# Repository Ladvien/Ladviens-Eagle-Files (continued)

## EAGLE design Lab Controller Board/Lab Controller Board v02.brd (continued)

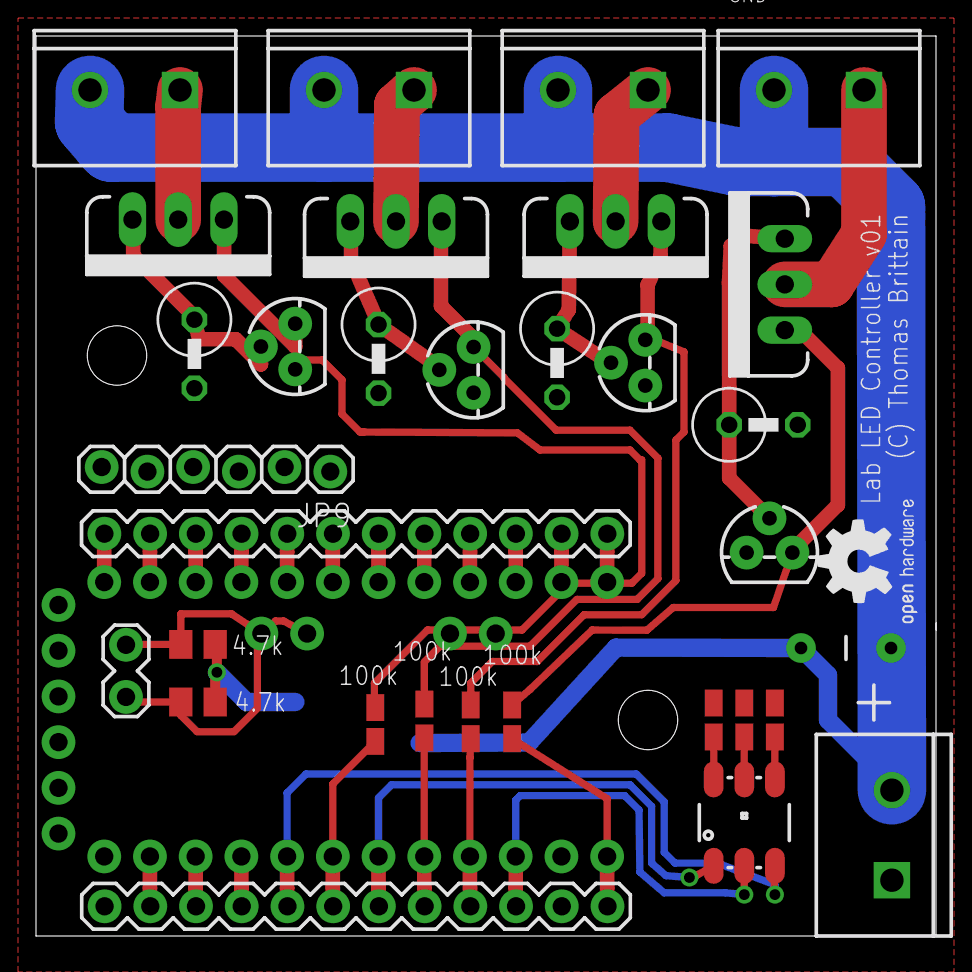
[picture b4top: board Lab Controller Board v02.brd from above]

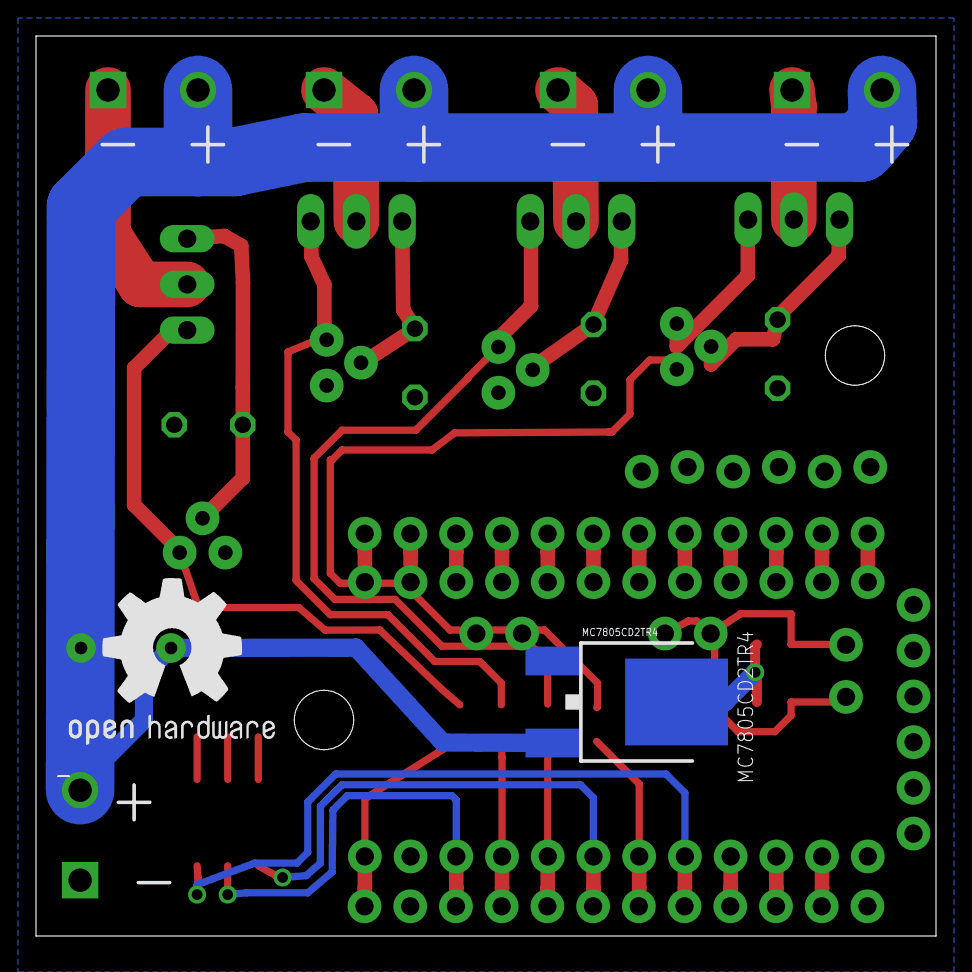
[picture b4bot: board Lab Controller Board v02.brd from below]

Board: 2 copper layers, 50.0 x 50.0 mm, 38 parts (2 on the bottom side), 44 nets.

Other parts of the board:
STANDOFF2: STAND-OFF

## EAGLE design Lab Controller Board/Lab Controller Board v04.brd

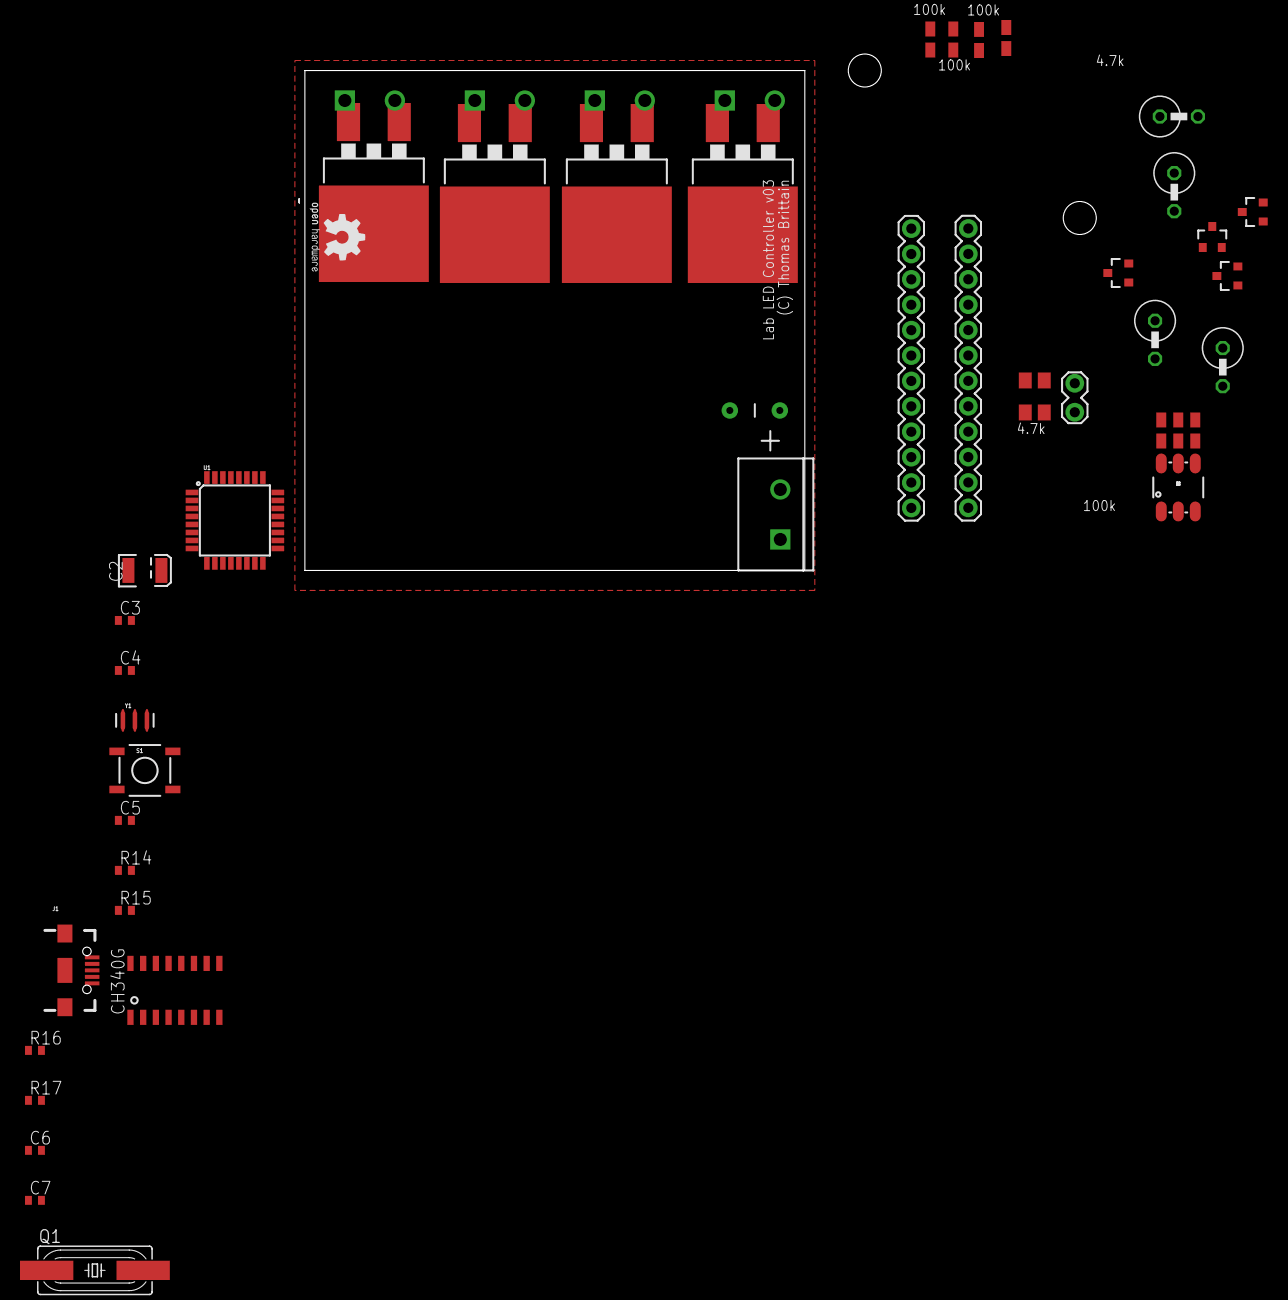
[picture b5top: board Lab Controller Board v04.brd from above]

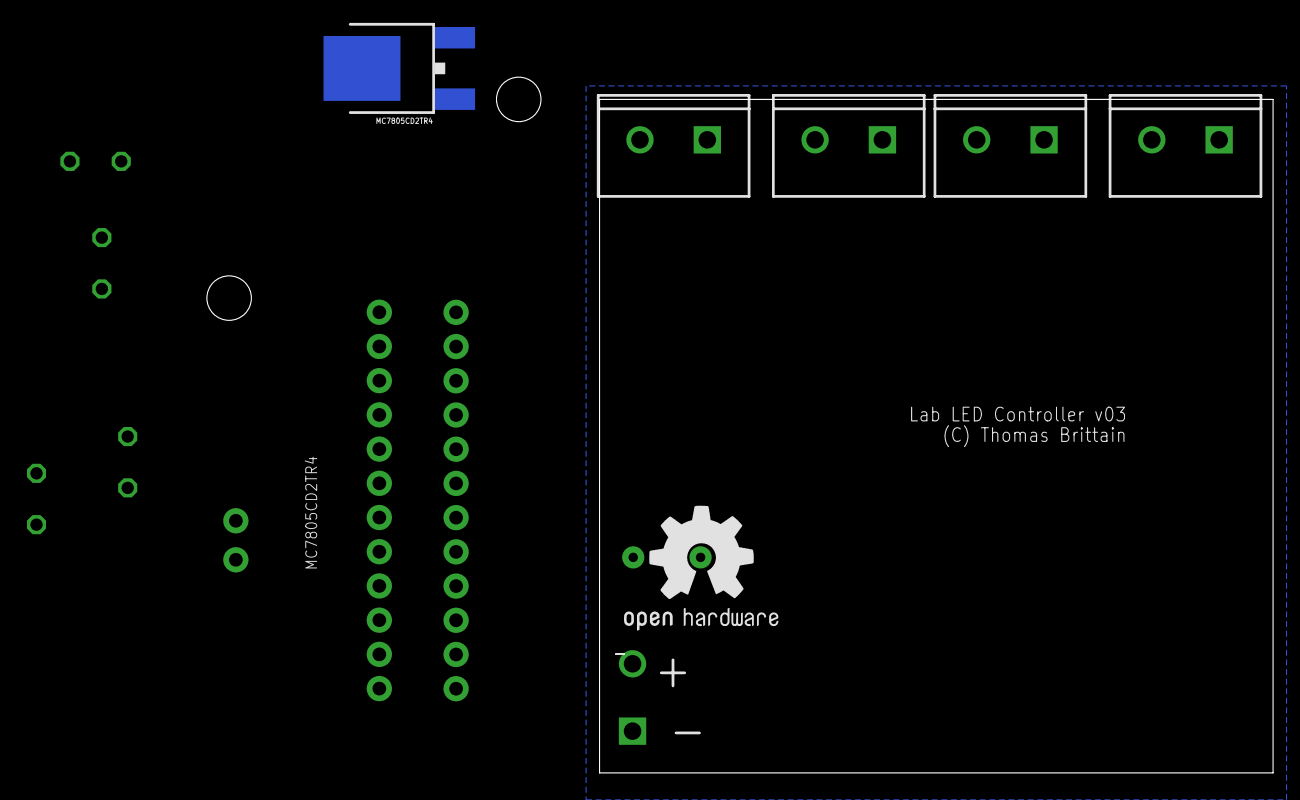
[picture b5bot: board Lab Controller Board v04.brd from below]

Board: 2 copper layers, 50.0 x 50.0 mm, 52 parts (6 on the bottom side), 42 nets, no tracks yet.

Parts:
C1: big; CAP-PTH-5MM
C2: 10uF; EIA3528
C3, C4, C5: 0.1uF; C0402
C6, C7: 22pF; C0402
FQP30N06L: 100A/100V; TO-263/D2PAK
GOLD_ORB_SM1: OSHWLOGO_GOLD_ORB_MED; OSHW1
GOLD_ORB_SM2: OSHWLOGO_GOLD_ORB_SM; OSHW2
J1: USB-B-MICRO-SMD_V03
JP1, JP2, JP3, JP4, JP5: SCREWTERMINAL-5MM-2
JP6, JP7: 1X12
JP8: 1X02_LOCK
LED1: LED-TRICOLOR-5050NO_IC; LED-TRICOLOR-5050
MC7805CD2TR4: V_REG_MC33269DT; DPAK
Q1: HC49UP
Q2, Q4, Q6, Q8: MMBT5088; SOT23-3
Q3, Q5, Q7: 100A/100V; TO-263/D2PAK
R1, R3, R5, R7, R11, R12, R13: 100k; R0805W
R2, R4, R6, R8: .75Ohm; 0411V
R9, R10: 4.7k; M0805
R14: 10k; R0402
R15: 330; R0402
R16, R17: 1k; R0402
S1: TAC_SWITCHSMD; TACTILE-SWITCH-SMD
STANDOFF1, STANDOFF2: STAND-OFF
U1: ATMEGA328P_TQFP; TQFP32-08
U2: CH340G; SOIC16
Y1: 16MHZ; RESONATOR-SMD

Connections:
5V: J1.VBUS, R9.2, R10.2, U2.16
12V: C1.1, JP1.2, JP2.2, JP3.2, JP4.2, JP5.2, MC7805CD2TR4.3
APM_PIN_3: JP6.7, R3.1
APM_PIN_5: JP6.5, R1.1
APM_PIN_6: JP6.4, R7.1
APM_PIN_9: JP6.1, R5.1
D+: J1.D+, U2.5
D-: J1.D-, U2.6
DTR: C5.1, U2.13
FET_SOURCE: FQP30N06L.3, Q2.1, R2.1
FET_SOURCE1: Q3.3, Q4.1, R4.1
FET_SOURCE2: Q5.3, Q6.1, R6.1
FET_SOURCE3: Q7.3, Q8.1, R8.1
GND: C1.2, C2.C, C3.2, C4.2, C6.2, C7.2, J1.GND, J1.ID, J1.SHIELD1, J1.SHIELD2, J1.SHIELD3, JP1.1, MC7805CD2TR4.1, Q2.2, Q4.2, Q6.2, Q8.2, R2.2, R4.2, R6.2, R8.2, R11.1, R12.1, R13.1, S1.1, S1.2, U1.3, U1.5, U1.21, U2.1, Y1.2
LED_DRAIN: FQP30N06L.2, JP2.1
LED_DRAIN1: JP5.1, Q3.2
LED_DRAIN2: JP4.1, Q5.2
LED_DRAIN3: JP3.1, Q7.2
unnamed: C3.1, U1.20
unnamed: U1.7, Y1.1
unnamed: JP6.8, LED1.3
unnamed: LED1.4, R11.2
unnamed: JP6.6, LED1.1
unnamed: LED1.6, R12.2
unnamed: LED1.5, R13.2
unnamed: U1.8, Y1.3
unnamed: JP7.1, JP7.2, JP7.3, JP7.4, JP7.5, JP7.6, JP7.7, JP7.8, JP7.9, JP7.10, JP7.11, JP7.12
unnamed: C5.2, R14.1, S1.3, S1.4, U1.29
unnamed: R15.2, U1.17
unnamed: U1.1, U1.2, U1.9, U1.10, U1.11, U1.12, U1.13, U1.14, U1.15, U1.16, U1.19, U1.22, U1.23, U1.24, U1.25, U1.26, U1.27, U1.28, U1.30, U1.31, U1.32
unnamed: U2.9, U2.10, U2.11, U2.12, U2.14, U2.15
unnamed: C6.1, C7.1, Q1.1, Q1.2, U2.4, U2.7, U2.8
POWER_LED: LED1.2, R15.1
PWM_B: FQP30N06L.1, Q2.3, R1.2
PWM_B1: Q3.1, Q4.3, R3.2
PWM_B2: Q5.1, Q6.3, R5.2
PWM_B3: Q7.1, Q8.3, R7.2
SCL: JP8.1, R10.1
SDA: JP8.2, R9.1
U2_RX: R17.2, U2.3
U2_TX: R16.2, U2.2
VCC: C2.A, C4.1, MC7805CD2TR4.4, R14.2, U1.4, U1.6, U1.18
